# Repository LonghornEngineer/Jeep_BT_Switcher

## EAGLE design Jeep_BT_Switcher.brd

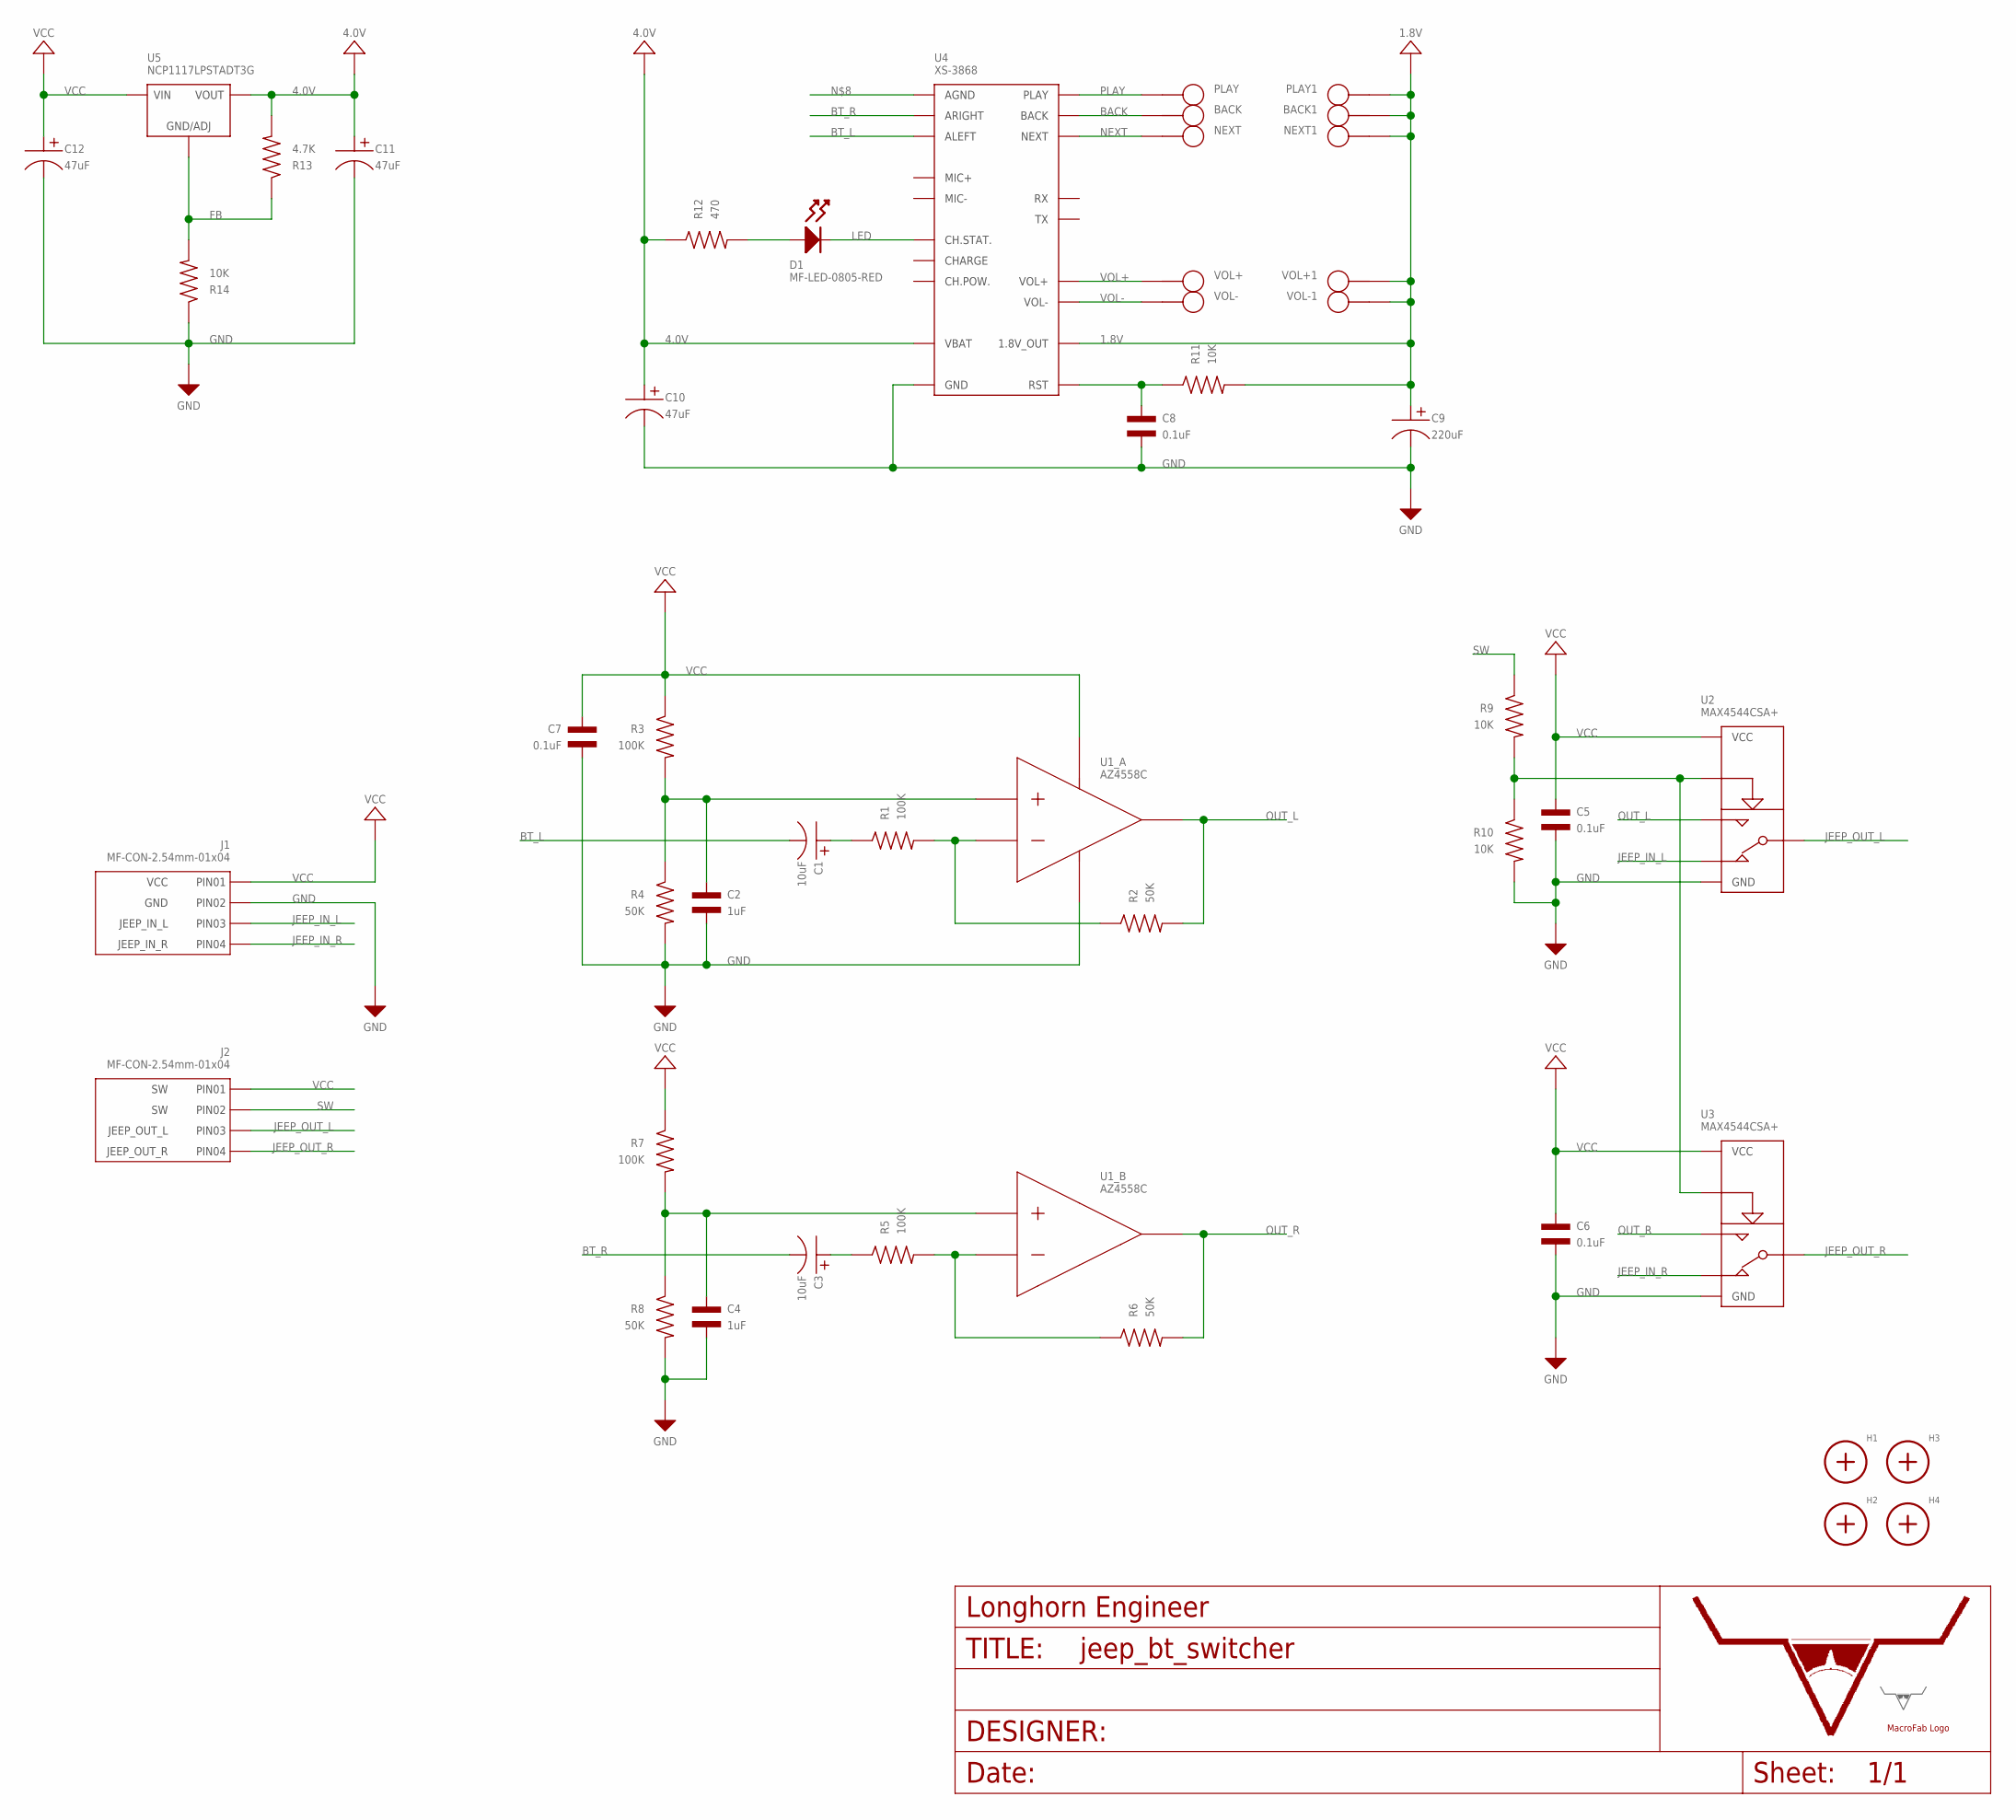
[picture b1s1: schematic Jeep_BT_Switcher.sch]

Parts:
BACK, BACK1: TEST_POINT_SINGLE_ROUND_1MM; ROUND_TP
C1, C3: 10uF; CP4MM
C2, C4: 1uF; C0805
C5, C6, C7, C8: 0.1uF; C0805
C9: 220uF; CP10MM
C10, C11, C12: 47uF; CP6.3MM
D1: MF-LED-0805-RED; LED0805
H1, H2, H3, H4: MOUNT_HOLE150MIL; MOUNT_HOLE_150MIL
J1, J2: MF-CON-2.54mm-01x04; PTH_2.54MM_01X04
NEXT, NEXT1: TEST_POINT_SINGLE_ROUND_1MM; ROUND_TP
PLAY, PLAY1: TEST_POINT_SINGLE_ROUND_1MM; ROUND_TP
R1, R3, R5, R7: 100K; R0805
R2, R4, R6, R8: 50K; R0805
R9, R10, R11, R14: 10K; R0805
R12: 470; R0805
R13: 4.7K; R0805
U1: AZ4558C; AZ4558C_SOIC-8
U2, U3: MAX4544CSA+; AZ4558C_SOIC-8
U4: XS-3868; XS3868
U5: NCP1117LPSTADT3G; SOT-223-3
U$11: LHE_FRAME
U$12: MF_LOGOLOGO_SMALL; MF_LOGO_SMALL
U$13: LHE_LOGOLHE_LOGO; LHE_LOGO
VOL+, VOL+1: TEST_POINT_SINGLE_ROUND_1MM; ROUND_TP
VOL-, VOL-1: TEST_POINT_SINGLE_ROUND_1MM; ROUND_TP

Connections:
1.8V: BACK1.P$1, C9.P$1, NEXT1.P$1, PLAY1.P$1, R11.P$2, U4.1.8V_OUT, VOL+1.P$1, VOL-1.P$1
4.0V: C10.P$1, C11.P$1, R12.P$1, R13.P$2, U4.VBAT, U5.P$1 (VOUT)
BACK: BACK.P$1, U4.BACK
BT_L: C1.P$2, U4.ALEFT
BT_R: C3.P$2, U4.ARIGHT
GND: C2.P$2, C4.P$2, C5.P$2, C6.P$2, C7.P$2, C8.P$2, C9.P$2, C10.P$2, C11.P$2, C12.P$2, J1.P$2 (PIN2), R4.P$2, R8.P$2, R10.P$2, R14.P$1, U1.4 (VEE), U2.4 (GND), U3.4 (GND), U4.GND
JEEP_IN_L: J1.P$3 (PIN3), U2.3 (NC)
JEEP_IN_R: J1.P$4 (PIN4), U3.3 (NC)
JEEP_OUT_L: J2.P$3 (PIN3), U2.2 (COM)
JEEP_OUT_R: J2.P$4 (PIN4), U3.2 (COM)
LED: D1.CATHODE, U4.CH.STAT.
unnamed: R1.P$2, R2.P$1, U1.2 (INPUT_1-)
unnamed: R5.P$2, R6.P$1, U1.6 (INPUT_2-)
unnamed: C1.P$1, R1.P$1
unnamed: C2.P$1, R3.P$2, R4.P$1, U1.3 (INPUT_1+)
unnamed: C3.P$1, R5.P$1
unnamed: C4.P$1, R7.P$2, R8.P$1, U1.5 (INPUT_2+)
unnamed: R9.P$2, R10.P$1, U2.7 (IN), U3.7 (IN)
unnamed: D1.ANODE, R12.P$2
NEXT: NEXT.P$1, U4.NEXT
unnamed: R13.P$1, R14.P$2, U5.P$2 (GND/ADJ)
OUT_L: R2.P$2, U1.1 (OUTPUT_1), U2.1 (NO)
OUT_R: R6.P$2, U1.7 (OUTPUT_2), U3.1 (NO)
PLAY: PLAY.P$1, U4.PLAY
RST: C8.P$1, R11.P$1, U4.RST
SW: J2.P$2 (PIN2), R9.P$1
VCC: C5.P$1, C6.P$1, C7.P$1, C12.P$1, J1.P$1 (PIN1), J2.P$1 (PIN1), R3.P$1, R7.P$1, U1.8 (VCC), U2.8 (VCC), U3.8 (VCC), U5.P$4 (VIN)
VOL+: U4.VOL+, VOL+.P$1
VOL-: U4.VOL-, VOL-.P$1

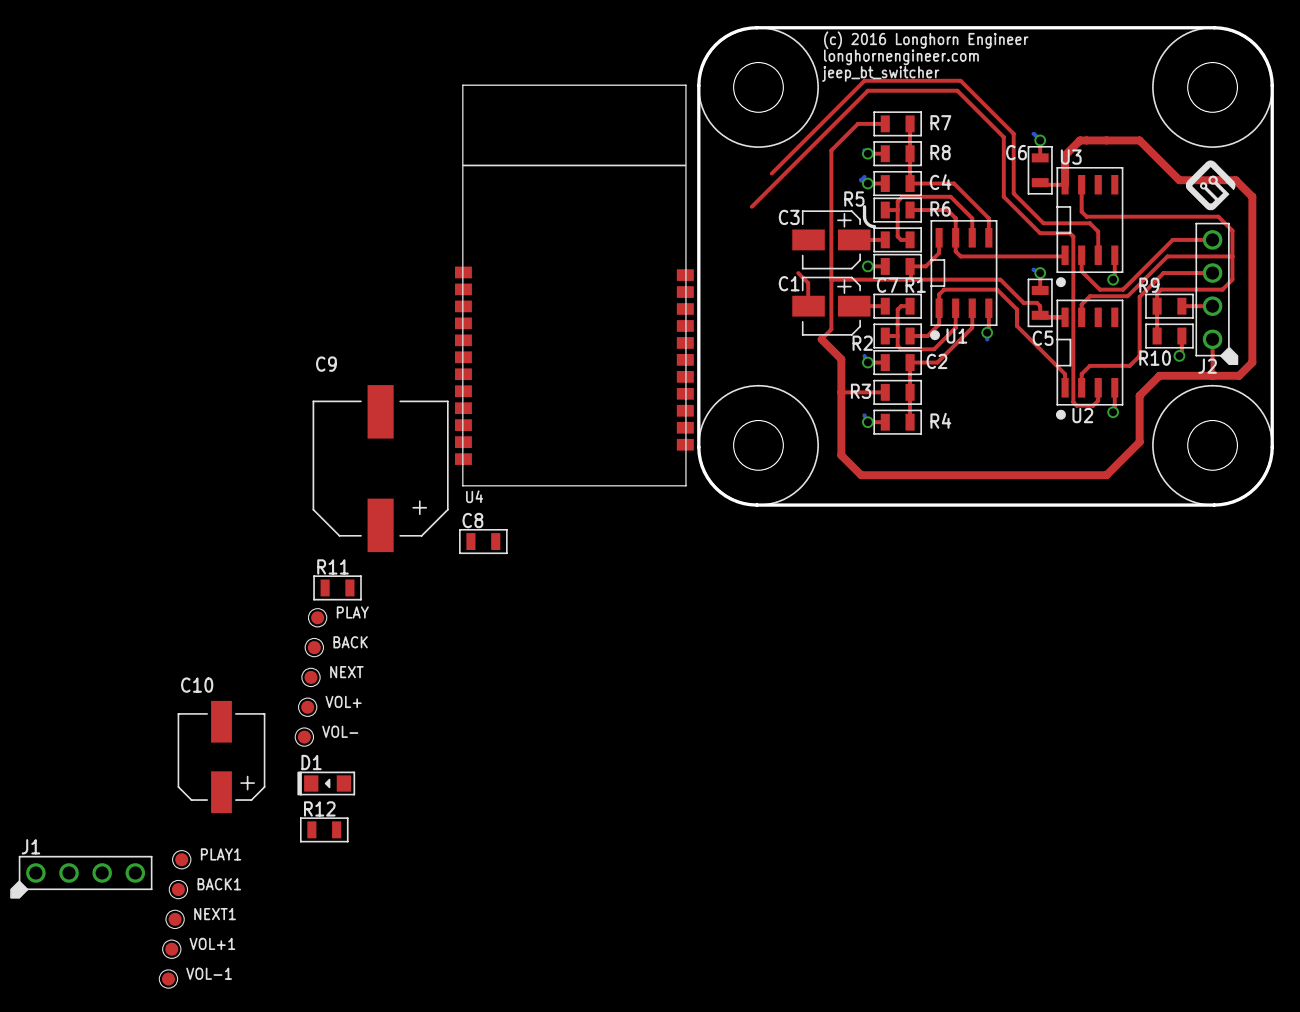
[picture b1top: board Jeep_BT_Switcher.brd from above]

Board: 2 copper layers, 43.9 x 36.6 mm, 46 parts (1 on the bottom side), 28 nets.

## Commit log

2016-12-23 first push of files.
2017-02-02 Added EXT power connector.
2017-02-02 Added cam files and XYRS
2017-02-06 Adding built in BT module.

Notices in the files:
parts and their libraries:
PP_Aesthetics: (c) 2016 Longhorn Engineer
